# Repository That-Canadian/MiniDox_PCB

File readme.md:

MiniDox PCB
===

These are the KiCad PCB source files for the MiniDox keyboard, created by u/That-Canadian on reddit

For the KiCad footprints/schematic libraries used please go to my [KiCad Library repo](https://github.com/That-Canadian/KiCad_Libs)

For case files / drawings see [DotDash32's Github](https://github.com/dotdash32/Cases/tree/master/Minidox)

For firmware files see the [QMK Github](https://github.com/qmk/qmk_firmware)

Copyright © 2017 Chirstopher Poole <maple-computing@vault-tech.net>
This work is free. You can redistribute it and/or modify it under the
terms of the Do What The Fuck You Want To Public License, Version 2,
as published by Sam Hocevar. See the LICENSE file for more details.

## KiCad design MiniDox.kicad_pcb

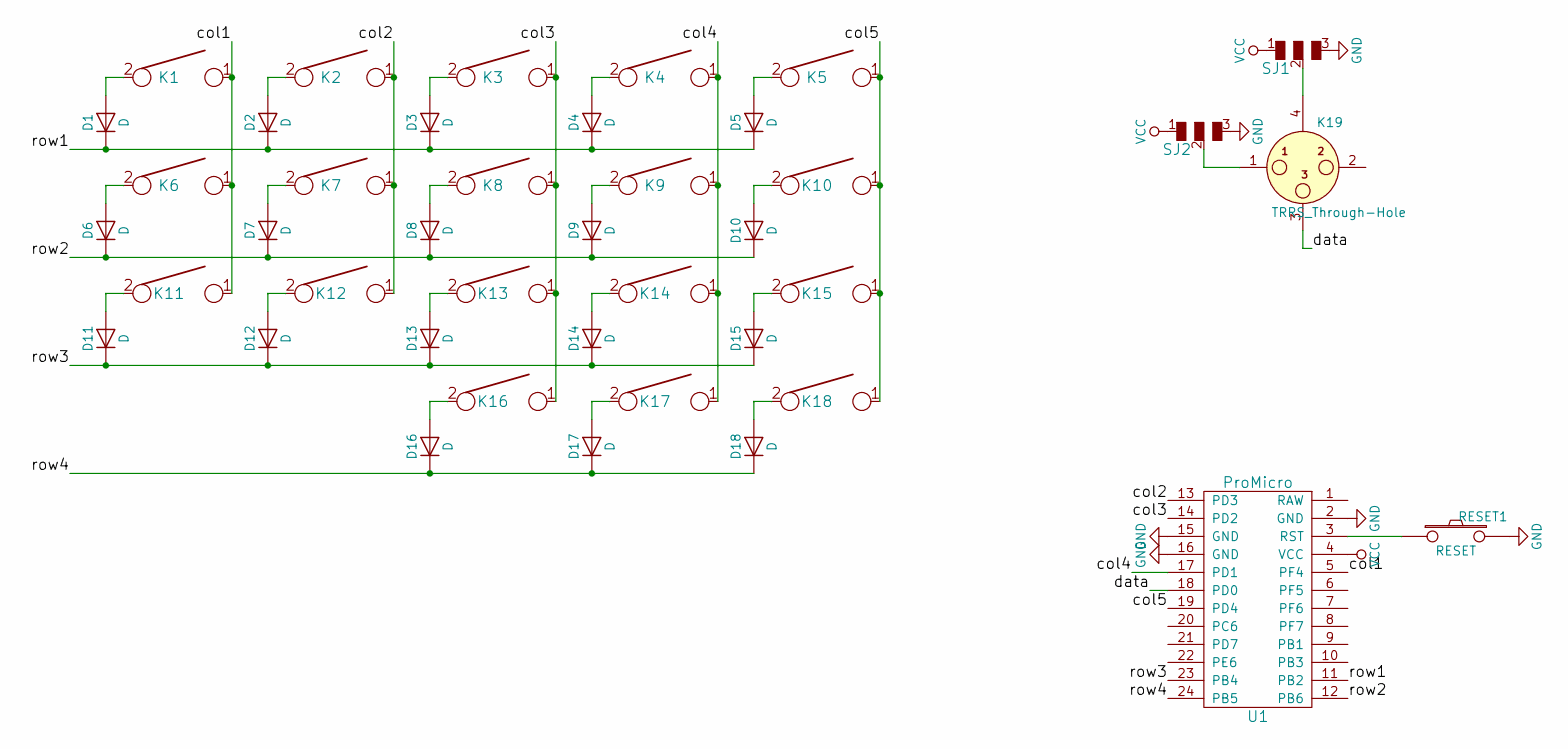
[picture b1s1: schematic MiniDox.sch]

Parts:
D1, D2, D3, D4, D5, D6, D7, D8, D9, D10, D11, D12, D13, D14, D15, D16, D17, D18: D; D_SOD123_axial-dual
K1, K2, K3, K4, K5, K6, K7, K8, K9, K10, K11, K12, K13, K14, K15, K16, K17: KEYSW; Mx_Alps_100-dualside
K18: KEYSW; Mx_Alps_175-dualside
K19: TRRS_Through-Hole; 4pin35mmAudio-dualsided
RESET1: RESET; SW_SPST_TL3342
SJ1, SJ2: SOLDER_JUMPER_3
U1: ProMicro; Pro_Micro

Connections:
/col1: K1.1, K6.1, K11.1, U1.5 (PF4)
/col2: K2.1, K7.1, K12.1, U1.13 (PD3)
/col3: K3.1, K8.1, K13.1, K16.1, U1.14 (PD2)
/col4: K4.1, K9.1, K14.1, K17.1, U1.17 (PD1)
/col5: K5.1, K10.1, K15.1, K18.1, U1.19 (PD4)
/data: K19.3, U1.18 (PD0)
/row1: D1.1 (K), D2.1 (K), D3.1 (K), D4.1 (K), D5.1 (K), U1.11 (PB2)
/row2: D6.1 (K), D7.1 (K), D8.1 (K), D9.1 (K), D10.1 (K), U1.12 (PB6)
/row3: D11.1 (K), D12.1 (K), D13.1 (K), D14.1 (K), D15.1 (K), U1.23 (PB4)
/row4: D16.1 (K), D17.1 (K), D18.1 (K), U1.24 (PB5)
GND: RESET1.2, SJ1.3, SJ2.3, U1.2 (GND), U1.15 (GND), U1.16 (GND); also elsewhere on the board
unnamed: D1.2 (A), K1.2
unnamed: D2.2 (A), K2.2
unnamed: D3.2 (A), K3.2
unnamed: D4.2 (A), K4.2
unnamed: D5.2 (A), K5.2
unnamed: D6.2 (A), K6.2
unnamed: D7.2 (A), K7.2
unnamed: D8.2 (A), K8.2
unnamed: D9.2 (A), K9.2
unnamed: D10.2 (A), K10.2
unnamed: D11.2 (A), K11.2
unnamed: D12.2 (A), K12.2
unnamed: D13.2 (A), K13.2
unnamed: D14.2 (A), K14.2
unnamed: D15.2 (A), K15.2
unnamed: D16.2 (A), K16.2
unnamed: D17.2 (A), K17.2
unnamed: D18.2 (A), K18.2
unnamed: K19.1, SJ2.2
unnamed: K19.4, SJ1.2
unnamed 32: RESET1.1, U1.3 (RST); also elsewhere on the board
VCC: SJ1.1, SJ2.1, U1.4 (VCC)

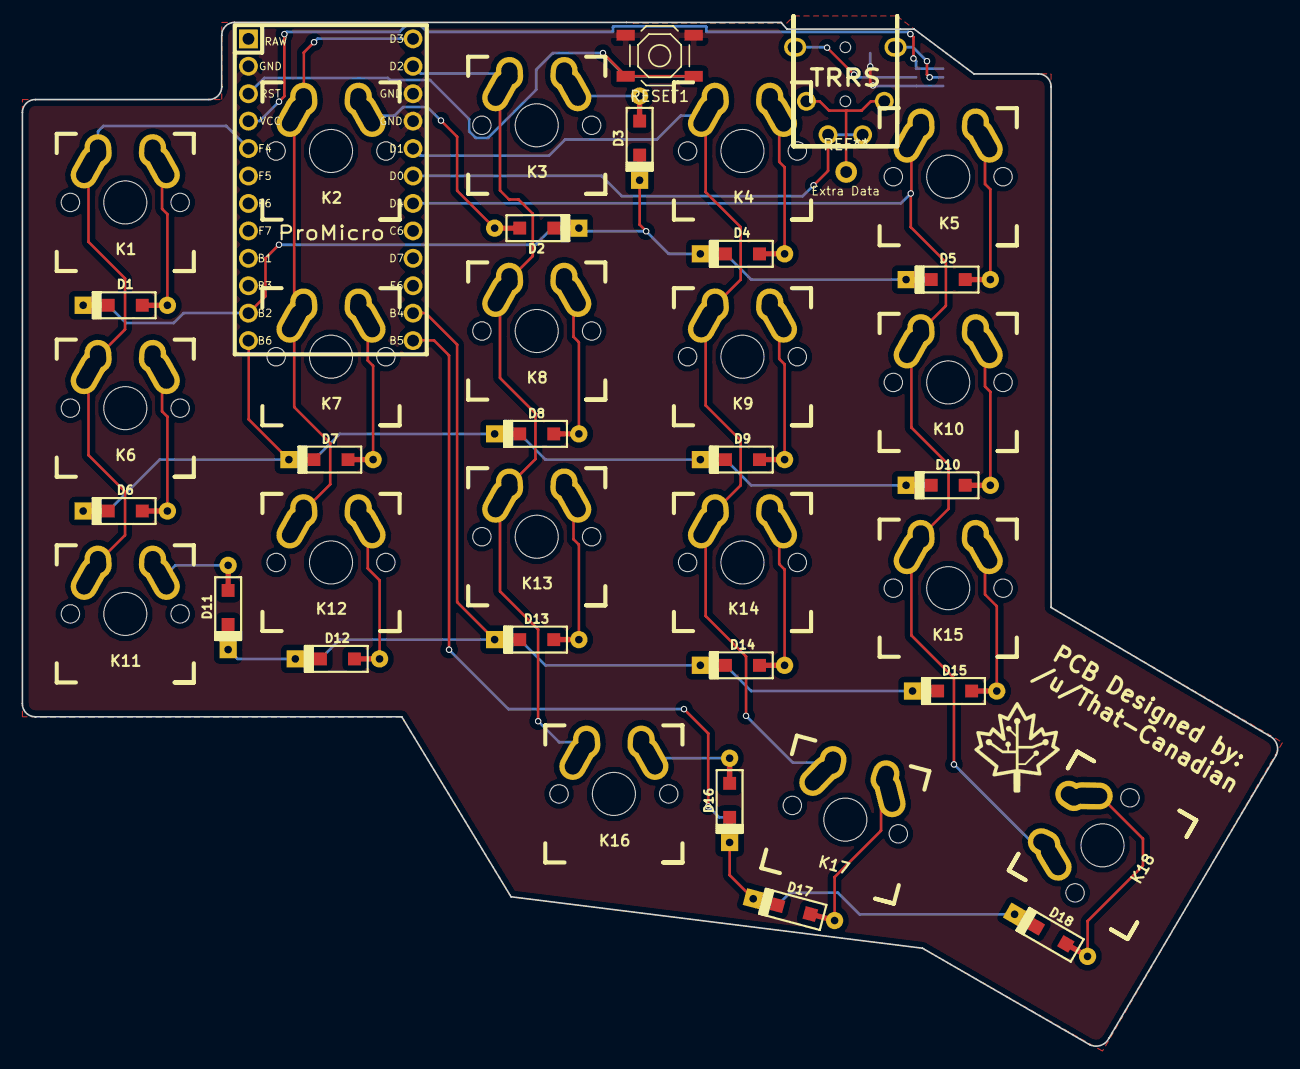
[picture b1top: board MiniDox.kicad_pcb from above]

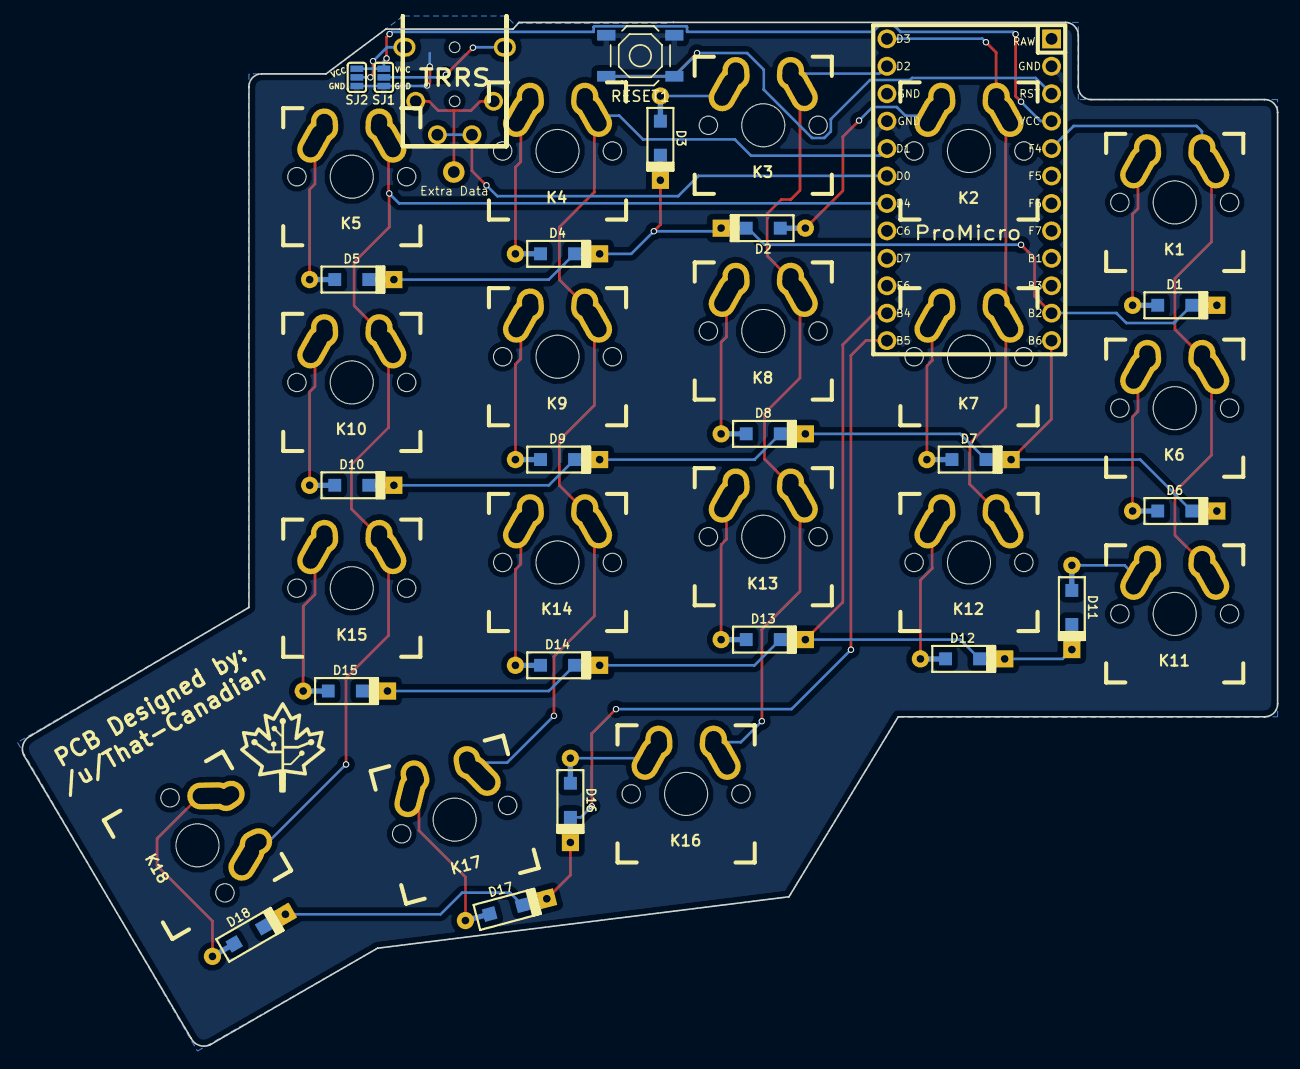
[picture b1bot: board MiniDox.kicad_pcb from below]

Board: 2 copper layers, 116.2 x 94.8 mm, 42 parts (21 on the bottom side), 33 nets.

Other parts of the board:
RESET1#2: RESET; SW_SPST_TL3342

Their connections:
GND: RESET1#2.2; also elsewhere on the board
unnamed 32: RESET1#2.1; also elsewhere on the board

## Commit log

2017-08-19 Initital commit, added MiniDox V1 files.
2017-08-19 Updated readme to be better
2017-08-20 Added WTFPL license
